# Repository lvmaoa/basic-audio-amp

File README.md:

Basic two stage gain amp with gain stage and buffer stage to practice BJT analysis for ECE 340

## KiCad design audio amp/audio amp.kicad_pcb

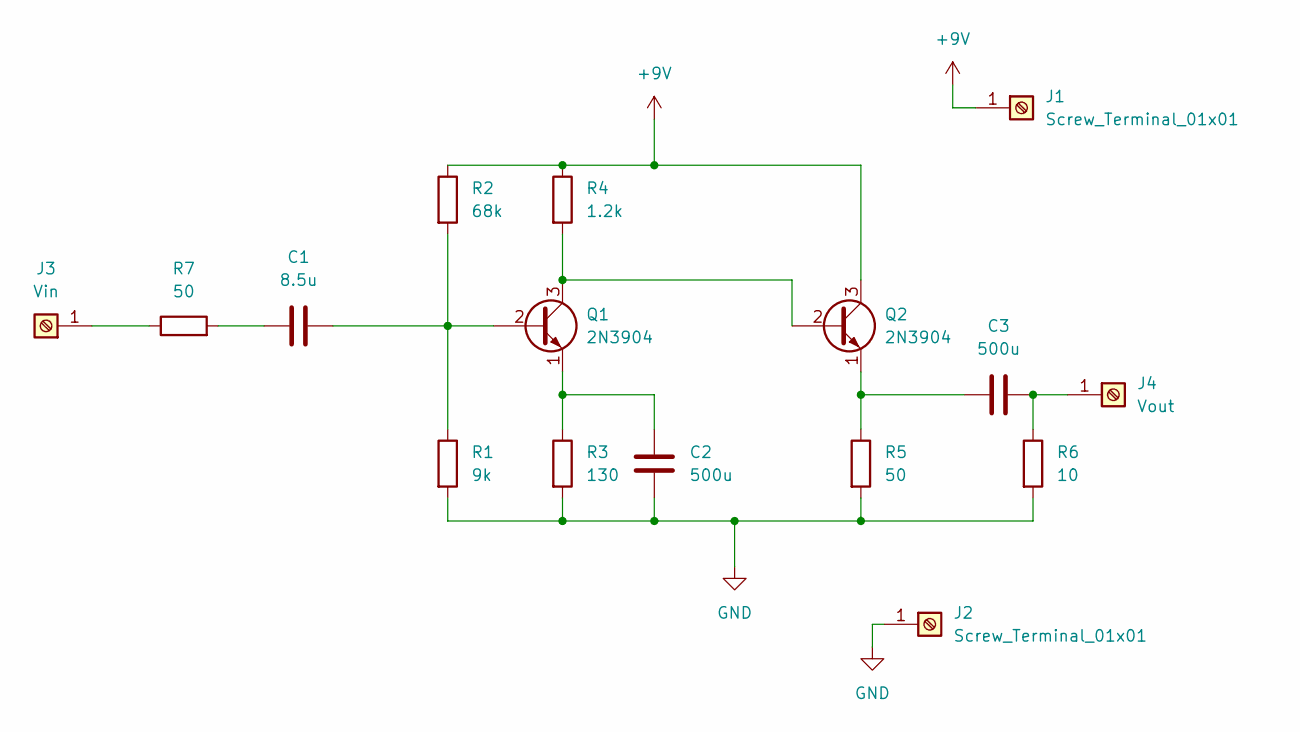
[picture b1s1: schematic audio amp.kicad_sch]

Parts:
C1: 8.5u; C_0805_2012Metric_Pad1.18x1.45mm_HandSolder
C2, C3: 500u; C_0805_2012Metric_Pad1.18x1.45mm_HandSolder
J1, J2: Screw_Terminal_01x01; TerminalBlock_MetzConnect_360271_1x01_Horizontal_ScrewM3.0_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
J3: Vin; TerminalBlock_MetzConnect_360271_1x01_Horizontal_ScrewM3.0_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
J4: Vout; TerminalBlock_MetzConnect_360271_1x01_Horizontal_ScrewM3.0_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
Q1, Q2: 2N3904; TO-92_Inline
R1: 9k; R_0805_2012Metric_Pad1.20x1.40mm_HandSolder
R2: 68k; R_0805_2012Metric_Pad1.20x1.40mm_HandSolder
R3: 130; R_0805_2012Metric_Pad1.20x1.40mm_HandSolder
R4: 1.2k; R_0805_2012Metric_Pad1.20x1.40mm_HandSolder
R5, R7: 50; R_0805_2012Metric_Pad1.20x1.40mm_HandSolder
R6: 10; R_0805_2012Metric_Pad1.20x1.40mm_HandSolder

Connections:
+9V: J1.1, Q2.3 (C), R2.1, R4.1
GND: C2.1, J2.1, R1.2, R3.2, R5.2, R6.2
unnamed: C1.1, R7.2
unnamed: J3.1, R7.1
unnamed: C3.1, J4.1, R6.1
unnamed: C1.2, Q1.2 (B), R1.1, R2.2
unnamed: Q1.3 (C), Q2.2 (B), R4.2
unnamed: C2.2, Q1.1 (E), R3.1
unnamed: C3.2, Q2.1 (E), R5.1

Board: 2 copper layers, 16 parts (0 on the bottom side), 9 nets, no tracks yet.

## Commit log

2024-02-16 Add files via upload
    init
2024-02-16 init image
2024-02-16 rename
